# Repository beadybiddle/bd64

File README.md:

# bd64
64 key custom mechanical keyboard project. Successor to the BD83.

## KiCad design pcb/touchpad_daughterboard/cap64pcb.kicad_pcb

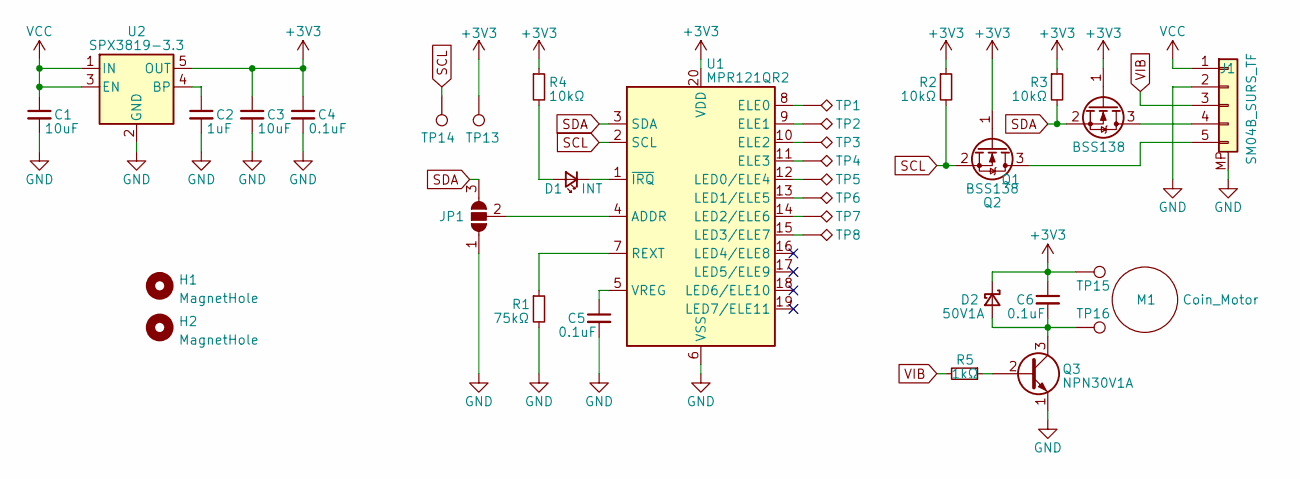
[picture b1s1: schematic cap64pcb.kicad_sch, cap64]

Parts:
C1, C3: 10uF; C_0805_2012Metric
C2: 1uF; C_0805_2012Metric
C4, C5, C6: 0.1uF; C_0805_2012Metric
D1: INT; LED_0603_1608Metric
D2: 50V1A; D_0805_2012Metric
H1, H2: MagnetHole; MountingHole_4mm
J1: SM04B_SURS_TF; JST_SUR_SM05B-SURS-TF_1x05-1MP_P0.80mm_Horizontal
JP1: SolderJumper_3_Open; SolderJumper-3_P1.3mm_Open_RoundedPad1.0x1.5mm_NumberLabels
M1: Coin_Motor; VC1018B001L
Q1, Q2: BSS138; SOT-23
Q3: NPN30V1A; SOT-23
R1: 75kΩ; R_0805_2012Metric
R2, R3, R4: 10kΩ; R_0805_2012Metric
R5: 1kΩ; R_0805_2012Metric
TP1: TestPoint_Alt; CAPPAD_11.4x11.6_1
TP2, TP3, TP4, TP5, TP6, TP7: TestPoint_Alt; CAPPAD_11.4x11.6_2
TP8: TestPoint_Alt; CAPPAD_11.4x11.6_3
TP13: b; TestPoint_Pad_D1.0mm
TP14: d; TestPoint_Pad_D1.0mm
TP15: +; TestPoint_Pad_1.0x1.0mm
TP16: -; TestPoint_Pad_1.0x1.0mm
U1: MPR121QR2; UQFN-20_3x3mm_P0.4mm
U2: SPX3819-3.3; SOT-23-5

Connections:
+3V3: C3.1, C4.1, C6.1, D2.1 (K), Q1.1 (G), Q2.1 (G), R2.1, R3.1, R4.1, TP13.1, TP15.1, U1.20 (VDD), U2.5 (OUT)
GND: C1.2, C2.2, C3.2, C4.2, C5.2, J1.2, J1.MP, JP1.1 (A), Q3.1 (E), R1.2, U1.6 (VSS), U2.2 (GND)
unnamed: C2.1, U2.4 (BP)
unnamed: C5.1, U1.5 (VREG)
unnamed: C6.2, D2.2 (A), Q3.3 (C), TP16.1
unnamed: D1.1 (K), U1.1 (~IRQ)
unnamed: D1.2 (A), R4.2
unnamed: J1.4, Q1.3 (D)
unnamed: J1.5, Q2.3 (D)
unnamed: JP1.2 (C), U1.4 (ADDR)
unnamed: Q3.2 (B), R5.1
unnamed: R1.1, U1.7 (REXT)
unnamed: TP1.1, U1.8 (ELE0)
unnamed: TP2.1, U1.9 (ELE1)
unnamed: TP3.1, U1.10 (ELE2)
unnamed: TP4.1, U1.11 (ELE3)
unnamed: TP5.1, U1.12 (LED0/ELE4)
unnamed: TP6.1, U1.13 (LED1/ELE5)
unnamed: TP7.1, U1.14 (LED2/ELE6)
unnamed: TP8.1, U1.15 (LED3/ELE7)
SCL: Q2.2 (S), R2.2, TP14.1, U1.2 (SCL)
SDA: JP1.3 (B), Q1.2 (S), R3.2, U1.3 (SDA)
VCC: C1.1, J1.1, U2.1 (IN), U2.3 (EN)
VIB: J1.3, R5.2

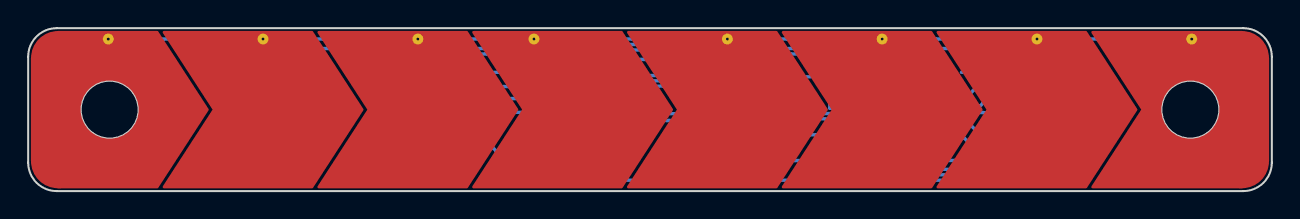
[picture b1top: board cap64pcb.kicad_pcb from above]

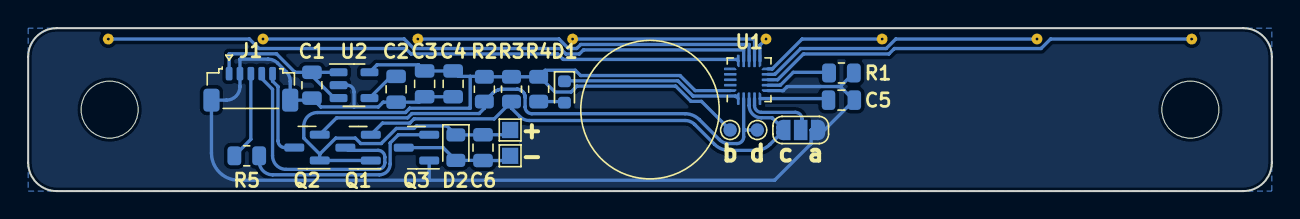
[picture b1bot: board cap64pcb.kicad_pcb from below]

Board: 2 copper layers, 91.6 x 12.0 mm, 35 parts (25 on the bottom side), 24 nets.

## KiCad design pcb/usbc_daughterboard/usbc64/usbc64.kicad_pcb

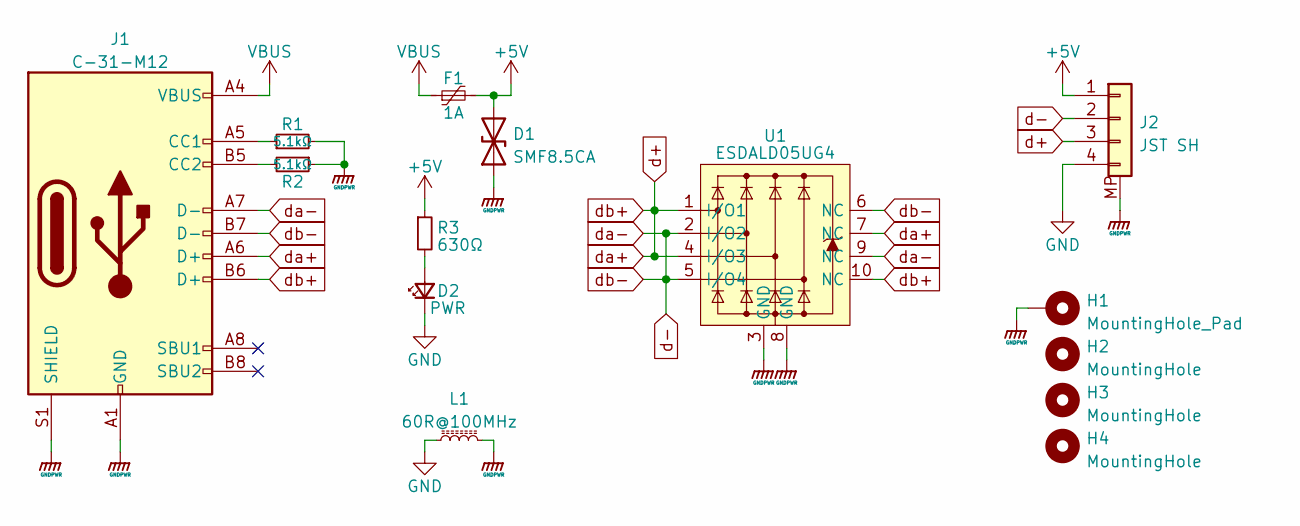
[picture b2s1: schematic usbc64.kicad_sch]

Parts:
D1: SMF8.5CA; D_SOD-123F
D2: PWR; LED_0603_1608Metric
F1: 1A; Fuse_1206_3216Metric
H1: MountingHole_Pad; MountingHole_2.2mm_M2_Pad
H2, H3, H4: MountingHole; MountingHole_2.2mm_M2_Pad
J1: C-31-M12; USB_C_Receptacle_HRO_TYPE-C-31-M-12
J2: JST SH; JST_SH_SM04B-SRSS-TB_1x04-1MP_P1.00mm_Horizontal
L1: 60R@100MHz; L_1206_3216Metric
R1, R2: 5.1kΩ; R_0603_1608Metric
R3: 630Ω; R_0603_1608Metric
U1: ESDALD05UG4

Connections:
+5V: D1.2 (A2), F1.2, J2.1, R3.1
GND: D2.1 (K), J2.4, L1.1
GNDPWR: D1.1 (A1), H1.1, J1.A1 (GND), J1.A12 (GND), J1.B1 (GND), J1.B12 (GND), J1.S1 (SHIELD), J2.MP, L1.2, R1.2, R2.1, U1.3 (GND), U1.8 (GND)
unnamed: D2.2 (A), R3.2
unnamed: J1.A5 (CC1), R1.1
unnamed: J1.B5 (CC2), R2.2
VBUS: F1.1, J1.A4 (VBUS), J1.A9 (VBUS), J1.B4 (VBUS), J1.B9 (VBUS)
d+: J1.A6 (D+), J1.B6 (D+), J2.3, U1.1 (I/O1), U1.4 (I/O3), U1.7 (NC), U1.10 (NC)
d-: J1.A7 (D-), J1.B7 (D-), J2.2, U1.2 (I/O2), U1.5 (I/O4), U1.6 (NC), U1.9 (NC)

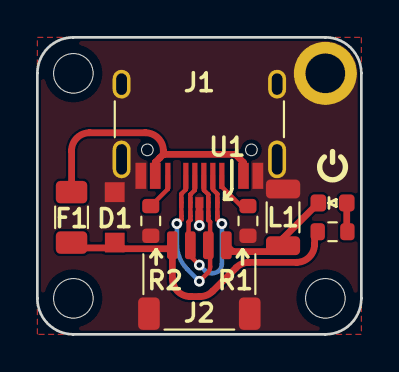
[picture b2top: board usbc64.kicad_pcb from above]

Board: 2 copper layers, 18.0 x 16.5 mm, 15 parts (1 on the bottom side), 9 nets.

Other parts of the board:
Ge: LOGO; usbc_back_silkraster

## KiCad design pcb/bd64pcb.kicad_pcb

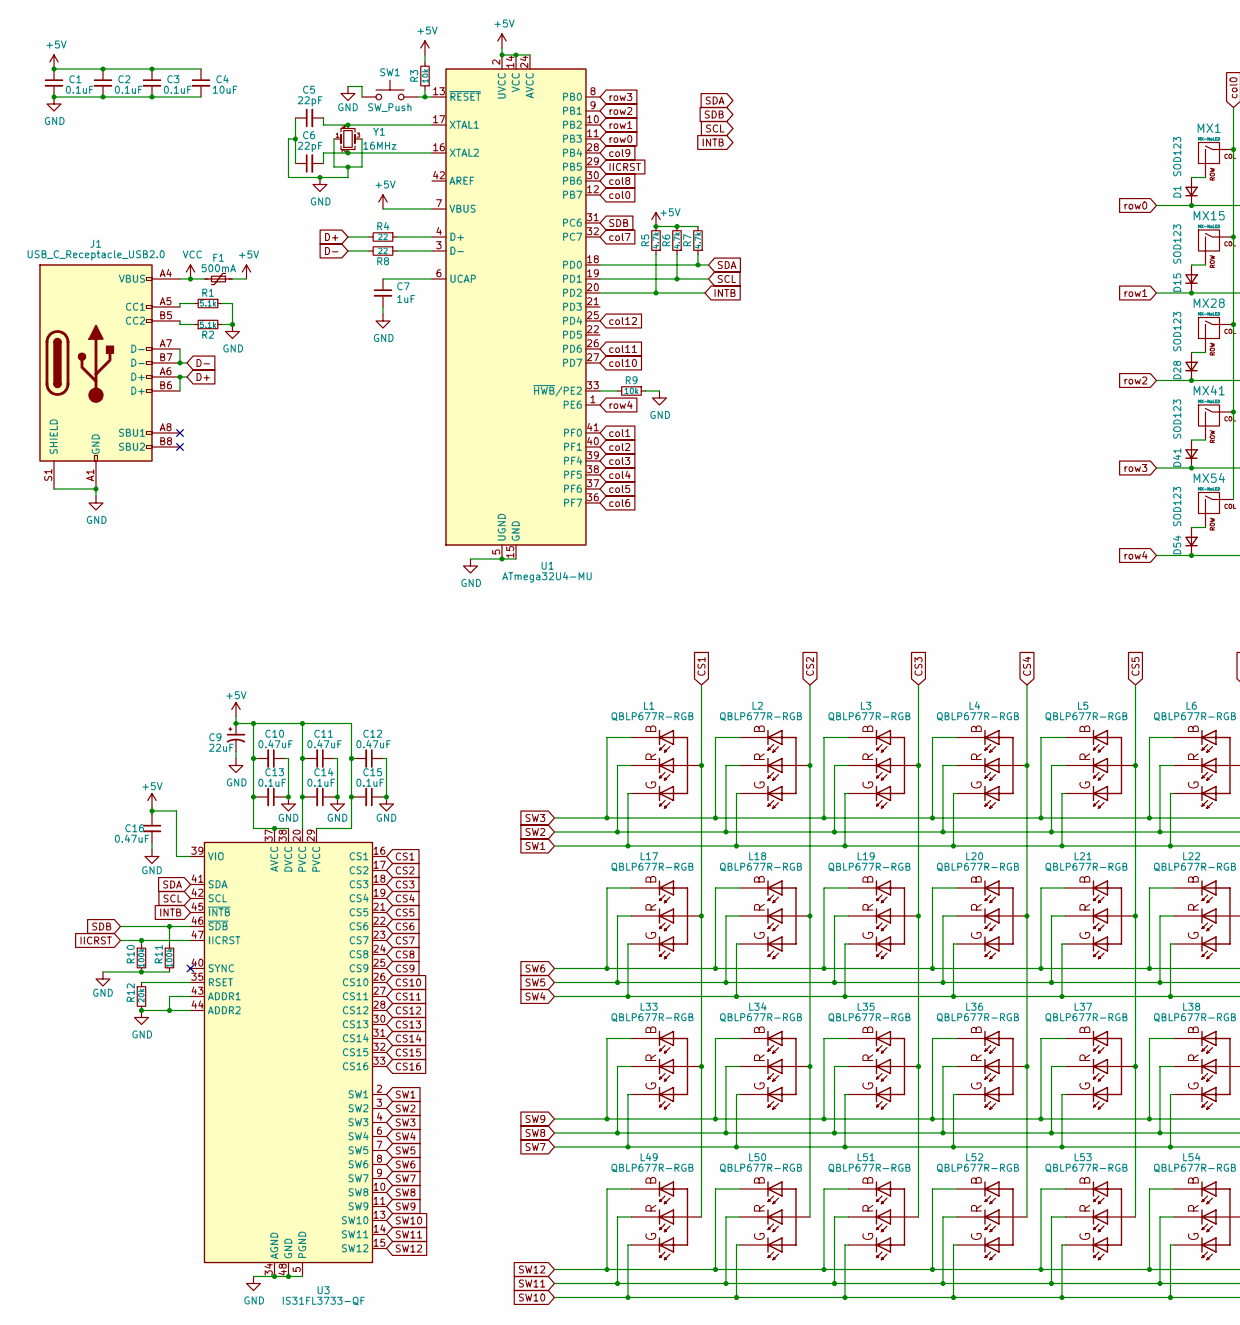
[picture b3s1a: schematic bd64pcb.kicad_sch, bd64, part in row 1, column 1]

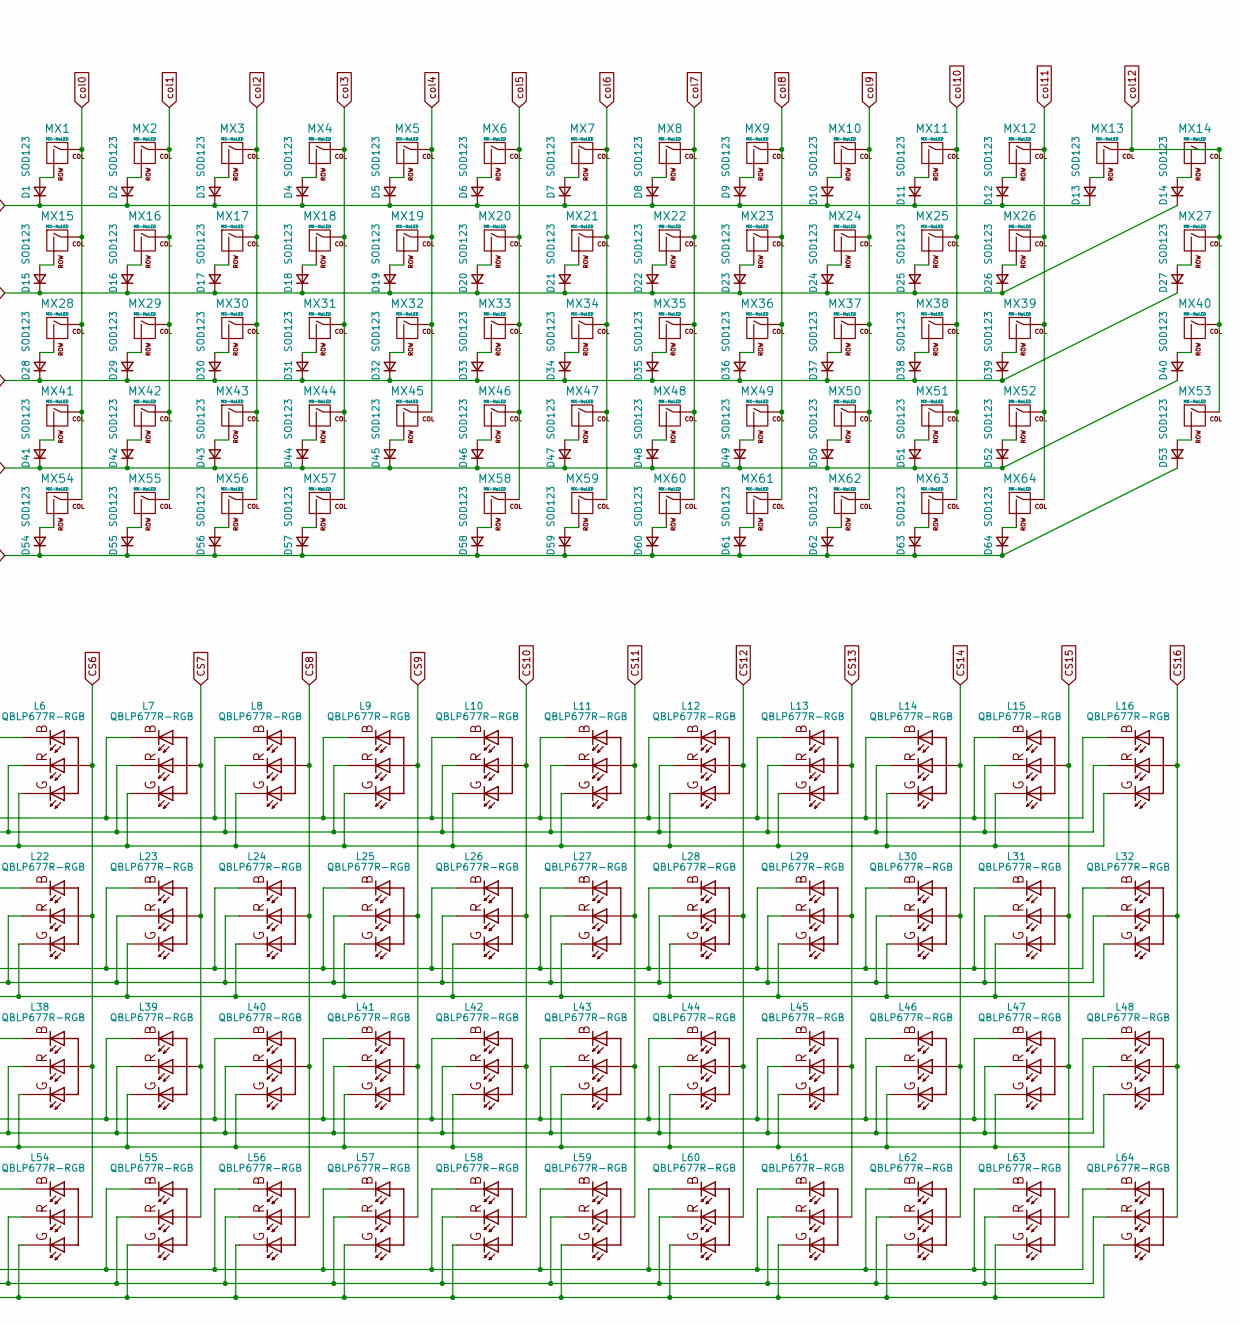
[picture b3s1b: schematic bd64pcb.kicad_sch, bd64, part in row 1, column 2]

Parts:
C1, C2, C3, C13, C14, C15: 0.1uF; C_0805_2012Metric
C4: 10uF; C_0805_2012Metric
C5, C6: 22pF; C_0805_2012Metric
C7: 1uF; C_0805_2012Metric
C9: 22uF; C_0805_2012Metric
C10, C11, C12, C16: 0.47uF; C_0805_2012Metric
D1, D2, D3, D4, D5, D6, D7, D8, D9, D10, D11, D12, D13, D14, D15, D16, D17, D18, D19, D20, D21, D22, D23, D24, D25, D26, D27, D28, D29, D30, D31, D32, D33, D34, D35, D36, D37, D38, D39, D40, D41, D42, D43, D44, D45, D46, D47, D48, D49, D50, D51, D52, D53, D54, D55, D56, D57, D58, D59, D60, D61, D62, D63, D64: SOD123; D_SOD-123
F1: 500mA; Fuse_1206_3216Metric
J1: USB_C_Receptacle_USB2.0; USB_C_Receptacle_GCT_USB4085
L1, L2, L3, L4, L5, L6, L7, L8, L9, L10, L11, L12, L13, L14, L15, L16, L17, L18, L19, L20, L21, L22, L23, L24, L25, L26, L27, L28, L29, L30, L31, L32, L33, L34, L35, L36, L37, L38, L39, L40, L41, L42, L43, L44, L45, L46, L47, L48, L49, L50, L51, L52, L53, L54, L55, L56, L57, L58, L59, L60, L61, L62, L63, L64: QBLP677R-RGB; RGB-REVERSE_MOUNT
MX1, MX2, MX3: MX-NoLED; MXOnly-1U-NoLED
MX4, MX5, MX6, MX7, MX8, MX9, MX10, MX11, MX12, MX13, MX14, MX16, MX17, MX18, MX19, MX20, MX21, MX22, MX23, MX24, MX25, MX26, MX29, MX30, MX31, MX32, MX33, MX34, MX35, MX36, MX37, MX38, MX39, MX42, MX43, MX44, MX45, MX46, MX47, MX48, MX49, MX50, MX51, MX52, MX58, MX59: MX-NoLED; MX-1U-NoLED
MX15, MX53, MX54, MX55, MX61, MX62, MX63, MX64: MX-NoLED; MX-1.25U-NoLED
MX27, MX41: MX-NoLED; MX-1.75U-NoLED
MX28, MX40, MX56, MX57, MX60: MX-NoLED; MX-1.5U-NoLED
R1, R2: 5.1k; R_0805_2012Metric
R3, R9: 10k; R_0805_2012Metric
R4, R8: 22; R_0805_2012Metric
R5, R6, R7: 4.7k; R_0805_2012Metric
R10, R11: 100k; R_0805_2012Metric
R12: 20k; R_0805_2012Metric
SW1: SW_Push; SKQG-1155865
U1: ATmega32U4-MU; QFN-44-1EP_7x7mm_P0.5mm_EP5.2x5.2mm
U3: IS31FL3733-QF; QFN-48-1EP_6x6mm_P0.4mm_EP4.2x4.2mm
Y1: 16MHz; Crystal_SMD_3225-4Pin_3.2x2.5mm

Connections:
+5V: C1.1, C2.1, C3.1, C4.1, C9.1, C10.2, C11.2, C12.2, C13.2, C14.2, C15.2, C16.1, F1.1, R3.2, R5.2, R6.2, R7.2, U1.2 (UVCC), U1.7 (VBUS), U1.14 (VCC), U1.24 (AVCC), U1.34 (VCC), U1.44 (AVCC), U3.20 (PVCC), U3.29 (PVCC), U3.37 (AVCC), U3.38 (DVCC), U3.39 (VIO)
CS1: L1.COMMON_ANODE, L17.COMMON_ANODE, L33.COMMON_ANODE, L49.COMMON_ANODE, U3.16 (CS1)
CS2: L2.COMMON_ANODE, L18.COMMON_ANODE, L34.COMMON_ANODE, L50.COMMON_ANODE, U3.17 (CS2)
CS3: L3.COMMON_ANODE, L19.COMMON_ANODE, L35.COMMON_ANODE, L51.COMMON_ANODE, U3.18 (CS3)
CS4: L4.COMMON_ANODE, L20.COMMON_ANODE, L36.COMMON_ANODE, L52.COMMON_ANODE, U3.19 (CS4)
CS5: L5.COMMON_ANODE, L21.COMMON_ANODE, L37.COMMON_ANODE, L53.COMMON_ANODE, U3.21 (CS5)
CS6: L6.COMMON_ANODE, L22.COMMON_ANODE, L38.COMMON_ANODE, L54.COMMON_ANODE, U3.22 (CS6)
CS7: L7.COMMON_ANODE, L23.COMMON_ANODE, L39.COMMON_ANODE, L55.COMMON_ANODE, U3.23 (CS7)
CS8: L8.COMMON_ANODE, L24.COMMON_ANODE, L40.COMMON_ANODE, L56.COMMON_ANODE, U3.24 (CS8)
CS9: L9.COMMON_ANODE, L25.COMMON_ANODE, L41.COMMON_ANODE, L57.COMMON_ANODE, U3.25 (CS9)
CS10: L10.COMMON_ANODE, L26.COMMON_ANODE, L42.COMMON_ANODE, L58.COMMON_ANODE, U3.26 (CS10)
CS11: L11.COMMON_ANODE, L27.COMMON_ANODE, L43.COMMON_ANODE, L59.COMMON_ANODE, U3.27 (CS11)
CS12: L12.COMMON_ANODE, L28.COMMON_ANODE, L44.COMMON_ANODE, L60.COMMON_ANODE, U3.28 (CS12)
CS13: L13.COMMON_ANODE, L29.COMMON_ANODE, L45.COMMON_ANODE, L61.COMMON_ANODE, U3.30 (CS13)
CS14: L14.COMMON_ANODE, L30.COMMON_ANODE, L46.COMMON_ANODE, L62.COMMON_ANODE, U3.31 (CS14)
CS15: L15.COMMON_ANODE, L31.COMMON_ANODE, L47.COMMON_ANODE, L63.COMMON_ANODE, U3.32 (CS15)
CS16: L16.COMMON_ANODE, L32.COMMON_ANODE, L48.COMMON_ANODE, L64.COMMON_ANODE, U3.33 (CS16)
D+: J1.A6 (D+), J1.B6 (D+), R4.2
D-: J1.A7 (D-), J1.B7 (D-), R8.2
GND: C1.2, C2.2, C3.2, C4.2, C5.1, C6.1, C7.2, C9.2, C10.1, C11.1, C12.1, C13.1, C14.1, C15.1, C16.2, J1.A1 (GND), J1.A12 (GND), J1.B1 (GND), J1.B12 (GND), J1.S1 (SHIELD), R1.1, R2.2, R9.1, R10.2, R11.2, R12.2, SW1.1, U1.5 (UGND), U1.15 (GND), U1.23 (GND), U1.35 (GND), U1.43 (GND), U1.45 (GND), U3.5 (PGND), U3.12 (PGND), U3.34 (AGND), U3.43 (ADDR1), U3.44 (ADDR2), U3.48 (GND), U3.49 (GND), Y1.1, Y1.3
IICRST: R10.1, U1.29 (PB5), U3.47 (IICRST)
INTB: R5.1, U1.20 (PD2), U3.45 (~INTB)
unnamed: C5.2, U1.17 (XTAL1), Y1.4
unnamed: C6.2, U1.16 (XTAL2), Y1.2
unnamed: C7.1, U1.6 (UCAP)
unnamed: D1.2 (A), MX1.2 (ROW)
unnamed: D2.2 (A), MX2.2 (ROW)
unnamed: D3.2 (A), MX3.2 (ROW)
unnamed: D4.2 (A), MX4.2 (ROW)
unnamed: D5.2 (A), MX5.2 (ROW)
unnamed: D6.2 (A), MX6.2 (ROW)
unnamed: D7.2 (A), MX7.2 (ROW)
unnamed: D8.2 (A), MX8.2 (ROW)
unnamed: D9.2 (A), MX9.2 (ROW)
unnamed: D10.2 (A), MX10.2 (ROW)
unnamed: D11.2 (A), MX11.2 (ROW)
unnamed: D12.2 (A), MX12.2 (ROW)
unnamed: D13.2 (A), MX13.2 (ROW)
unnamed: D14.2 (A), MX14.2 (ROW)
unnamed: D15.2 (A), MX15.2 (ROW)
unnamed: D16.2 (A), MX16.2 (ROW)
unnamed: D17.2 (A), MX17.2 (ROW)
unnamed: D18.2 (A), MX18.2 (ROW)
unnamed: D19.2 (A), MX19.2 (ROW)
unnamed: D20.2 (A), MX20.2 (ROW)
unnamed: D21.2 (A), MX21.2 (ROW)
unnamed: D22.2 (A), MX22.2 (ROW)
unnamed: D23.2 (A), MX23.2 (ROW)
unnamed: D24.2 (A), MX24.2 (ROW)
unnamed: D25.2 (A), MX25.2 (ROW)
unnamed: D26.2 (A), MX26.2 (ROW)
unnamed: D27.2 (A), MX27.2 (ROW)
unnamed: D28.2 (A), MX28.2 (ROW)
unnamed: D29.2 (A), MX29.2 (ROW)
unnamed: D30.2 (A), MX30.2 (ROW)
unnamed: D31.2 (A), MX31.2 (ROW)
unnamed: D32.2 (A), MX32.2 (ROW)
unnamed: D33.2 (A), MX33.2 (ROW)
unnamed: D34.2 (A), MX34.2 (ROW)
unnamed: D35.2 (A), MX35.2 (ROW)
unnamed: D36.2 (A), MX36.2 (ROW)
unnamed: D37.2 (A), MX37.2 (ROW)
unnamed: D38.2 (A), MX38.2 (ROW)
unnamed: D39.2 (A), MX39.2 (ROW)
unnamed: D40.2 (A), MX40.2 (ROW)
unnamed: D41.2 (A), MX41.2 (ROW)
unnamed: D42.2 (A), MX42.2 (ROW)
unnamed: D43.2 (A), MX43.2 (ROW)
unnamed: D44.2 (A), MX44.2 (ROW)
unnamed: D45.2 (A), MX45.2 (ROW)
unnamed: D46.2 (A), MX46.2 (ROW)
unnamed: D47.2 (A), MX47.2 (ROW)
unnamed: D48.2 (A), MX48.2 (ROW)
unnamed: D49.2 (A), MX49.2 (ROW)
unnamed: D50.2 (A), MX50.2 (ROW)
unnamed: D51.2 (A), MX51.2 (ROW)
unnamed: D52.2 (A), MX52.2 (ROW)
unnamed: D53.2 (A), MX53.2 (ROW)
unnamed: D54.2 (A), MX54.2 (ROW)
unnamed: D55.2 (A), MX55.2 (ROW)
unnamed: D56.2 (A), MX56.2 (ROW)
unnamed: D57.2 (A), MX57.2 (ROW)
unnamed: D58.2 (A), MX58.2 (ROW)
unnamed: D59.2 (A), MX59.2 (ROW)
unnamed: D60.2 (A), MX60.2 (ROW)
unnamed: D61.2 (A), MX61.2 (ROW)
unnamed: D62.2 (A), MX62.2 (ROW)
unnamed: D63.2 (A), MX63.2 (ROW)
unnamed: D64.2 (A), MX64.2 (ROW)
unnamed: J1.A5 (CC1), R1.2
unnamed: J1.B5 (CC2), R2.1
unnamed: R3.1, SW1.2, U1.13 (~RESET)
unnamed: R4.1, U1.4 (D+)
unnamed: R8.1, U1.3 (D-)
unnamed: R9.2, U1.33 (~HWB/PE2)
unnamed: R12.1, U3.35 (RSET)
SCL: R6.1, U1.19 (PD1), U3.42 (SCL)
SDA: R7.1, U1.18 (PD0), U3.41 (SDA)
SDB: R11.1, U1.31 (PC6), U3.46 (~SDB)
SW1: L1.2, L2.2, L3.2, L4.2, L5.2, L6.2, L7.2, L8.2, L9.2, L10.2, L11.2, L12.2, L13.2, L14.2, L15.2, L16.2, U3.2 (SW1)
SW2: L1.3, L2.3, L3.3, L4.3, L5.3, L6.3, L7.3, L8.3, L9.3, L10.3, L11.3, L12.3, L13.3, L14.3, L15.3, L16.3, U3.3 (SW2)
SW3: L1.1, L2.1, L3.1, L4.1, L5.1, L6.1, L7.1, L8.1, L9.1, L10.1, L11.1, L12.1, L13.1, L14.1, L15.1, L16.1, U3.4 (SW3)
SW4: L17.2, L18.2, L19.2, L20.2, L21.2, L22.2, L23.2, L24.2, L25.2, L26.2, L27.2, L28.2, L29.2, L30.2, L31.2, L32.2, U3.6 (SW4)
SW5: L17.3, L18.3, L19.3, L20.3, L21.3, L22.3, L23.3, L24.3, L25.3, L26.3, L27.3, L28.3, L29.3, L30.3, L31.3, L32.3, U3.7 (SW5)
SW6: L17.1, L18.1, L19.1, L20.1, L21.1, L22.1, L23.1, L24.1, L25.1, L26.1, L27.1, L28.1, L29.1, L30.1, L31.1, L32.1, U3.8 (SW6)
SW7: L33.2, L34.2, L35.2, L36.2, L37.2, L38.2, L39.2, L40.2, L41.2, L42.2, L43.2, L44.2, L45.2, L46.2, L47.2, L48.2, U3.9 (SW7)
SW8: L33.3, L34.3, L35.3, L36.3, L37.3, L38.3, L39.3, L40.3, L41.3, L42.3, L43.3, L44.3, L45.3, L46.3, L47.3, L48.3, U3.10 (SW8)
SW9: L33.1, L34.1, L35.1, L36.1, L37.1, L38.1, L39.1, L40.1, L41.1, L42.1, L43.1, L44.1, L45.1, L46.1, L47.1, L48.1, U3.11 (SW9)
SW10: L49.2, L50.2, L51.2, L52.2, L53.2, L54.2, L55.2, L56.2, L57.2, L58.2, L59.2, L60.2, L61.2, L62.2, L63.2, L64.2, U3.13 (SW10)
SW11: L49.3, L50.3, L51.3, L52.3, L53.3, L54.3, L55.3, L56.3, L57.3, L58.3, L59.3, L60.3, L61.3, L62.3, L63.3, L64.3, U3.14 (SW11)
SW12: L49.1, L50.1, L51.1, L52.1, L53.1, L54.1, L55.1, L56.1, L57.1, L58.1, L59.1, L60.1, L61.1, L62.1, L63.1, L64.1, U3.15 (SW12)
VCC: F1.2, J1.A4 (VBUS), J1.A9 (VBUS), J1.B4 (VBUS), J1.B9 (VBUS)
col0: MX1.1 (COL), MX15.1 (COL), MX28.1 (COL), MX41.1 (COL), MX54.1 (COL), U1.12 (PB7)
col1: MX2.1 (COL), MX16.1 (COL), MX29.1 (COL), MX42.1 (COL), MX55.1 (COL), U1.41 (PF0)
col2: MX3.1 (COL), MX17.1 (COL), MX30.1 (COL), MX43.1 (COL), MX56.1 (COL), U1.40 (PF1)
col3: MX4.1 (COL), MX18.1 (COL), MX31.1 (COL), MX44.1 (COL), MX57.1 (COL), U1.39 (PF4)
col4: MX5.1 (COL), MX19.1 (COL), MX32.1 (COL), MX45.1 (COL), U1.38 (PF5)
col5: MX6.1 (COL), MX20.1 (COL), MX33.1 (COL), MX46.1 (COL), MX58.1 (COL), U1.37 (PF6)
col6: MX7.1 (COL), MX21.1 (COL), MX34.1 (COL), MX47.1 (COL), MX59.1 (COL), U1.36 (PF7)
col7: MX8.1 (COL), MX22.1 (COL), MX35.1 (COL), MX48.1 (COL), MX60.1 (COL), U1.32 (PC7)
col8: MX9.1 (COL), MX23.1 (COL), MX36.1 (COL), MX49.1 (COL), MX61.1 (COL), U1.30 (PB6)
col9: MX10.1 (COL), MX24.1 (COL), MX37.1 (COL), MX50.1 (COL), MX62.1 (COL), U1.28 (PB4)
col10: MX11.1 (COL), MX25.1 (COL), MX38.1 (COL), MX51.1 (COL), MX63.1 (COL), U1.27 (PD7)
col11: MX12.1 (COL), MX26.1 (COL), MX39.1 (COL), MX52.1 (COL), MX64.1 (COL), U1.26 (PD6)
col12: MX13.1 (COL), MX14.1 (COL), MX27.1 (COL), MX40.1 (COL), MX53.1 (COL), U1.25 (PD4)
row0: D1.1 (K), D2.1 (K), D3.1 (K), D4.1 (K), D5.1 (K), D6.1 (K), D7.1 (K), D8.1 (K), D9.1 (K), D10.1 (K), D11.1 (K), D12.1 (K), D13.1 (K), U1.11 (PB3)
row1: D14.1 (K), D15.1 (K), D16.1 (K), D17.1 (K), D18.1 (K), D19.1 (K), D20.1 (K), D21.1 (K), D22.1 (K), D23.1 (K), D24.1 (K), D25.1 (K), D26.1 (K), U1.10 (PB2)
row2: D27.1 (K), D28.1 (K), D29.1 (K), D30.1 (K), D31.1 (K), D32.1 (K), D33.1 (K), D34.1 (K), D35.1 (K), D36.1 (K), D37.1 (K), D38.1 (K), D39.1 (K), U1.9 (PB1)
row3: D40.1 (K), D41.1 (K), D42.1 (K), D43.1 (K), D44.1 (K), D45.1 (K), D46.1 (K), D47.1 (K), D48.1 (K), D49.1 (K), D50.1 (K), D51.1 (K), D52.1 (K), U1.8 (PB0)
row4: D53.1 (K), D54.1 (K), D55.1 (K), D56.1 (K), D57.1 (K), D58.1 (K), D59.1 (K), D60.1 (K), D61.1 (K), D62.1 (K), D63.1 (K), D64.1 (K), U1.1 (PE6)

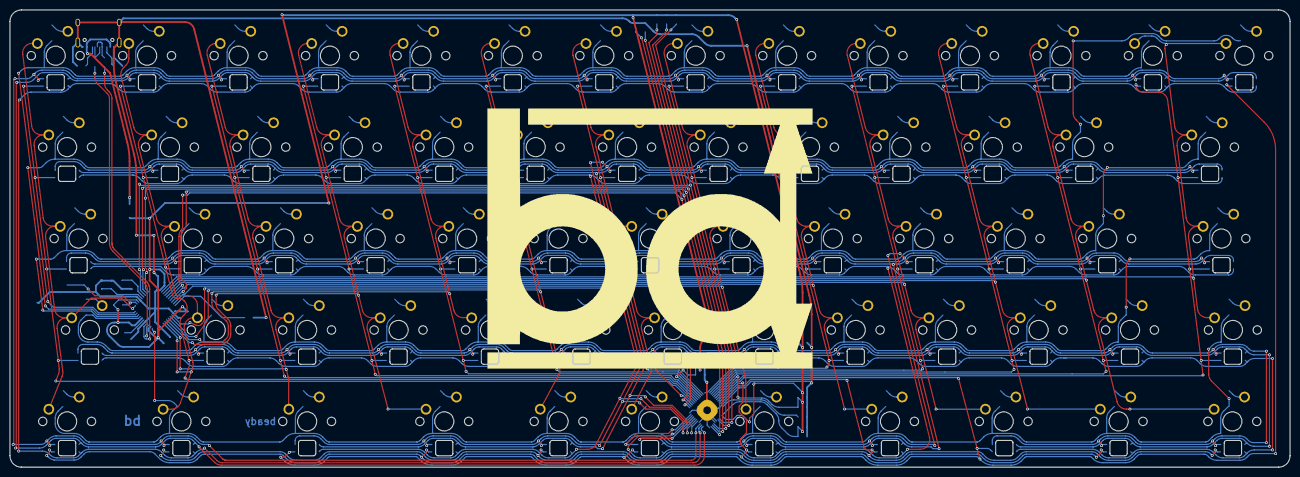
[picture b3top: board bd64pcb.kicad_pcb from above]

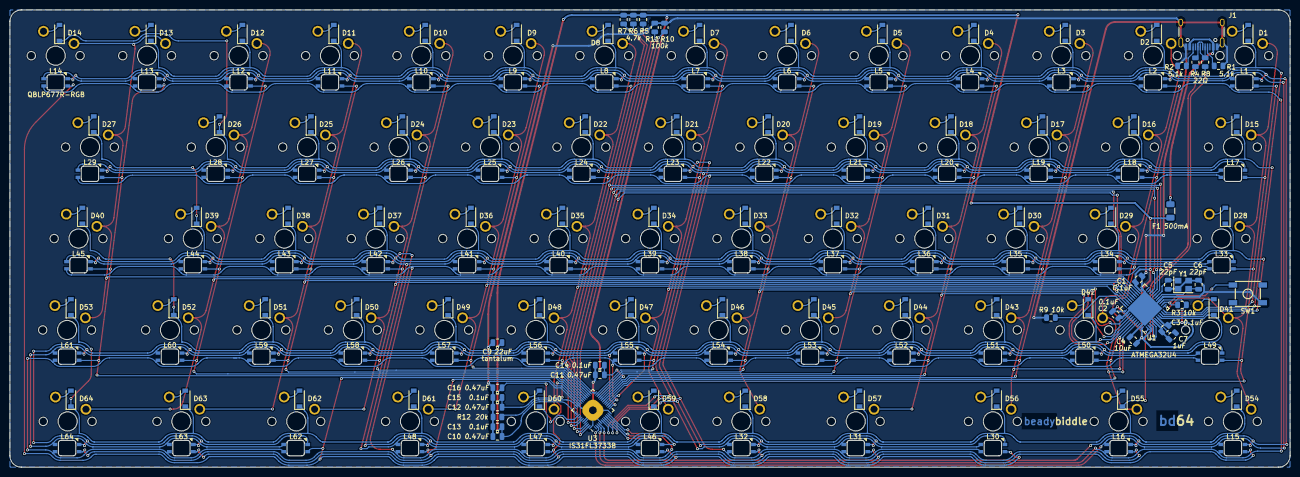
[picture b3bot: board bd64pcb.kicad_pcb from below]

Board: 2 copper layers, 266.7 x 95.2 mm, 225 parts (161 on the bottom side), 130 nets.

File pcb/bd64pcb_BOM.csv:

"Id";"Designator";"Package";"Quantity";"Designation";"Supplier and ref";
1;"MX1,MX2,MX4,MX10,MX11,MX12,MX13,MX14,MX16,MX17,MX18,MX19,MX20,MX25,MX26,MX29,MX37,MX38,MX39,MX42,MX43,MX44,MX45,MX46,MX47,MX48,MX49,MX50,MX51,MX52,MX58,MX59,MX30,MX36,MX35,MX34,MX33,MX32,MX31,MX23,MX22,MX21,MX5,MX9,MX24,MX7,MX6,MX8,MX3";"MXOnly-1U-NoLED";49;"MX-NoLED";;;
2;"MX15,MX54,MX55,MX61,MX62,MX63,MX64,MX53";"MXOnly-1.25U-NoLED";8;"MX-NoLED";;;
3;"MX28,MX40,MX56,MX57,MX60";"MXOnly-1.5U-NoLED";5;"MX-NoLED";;;
4;"MX41,MX27";"MXOnly-1.75U-NoLED";2;"MX-NoLED";;;
5;"C1,C2,C3,C13,C14,C15";"C_0805_2012Metric";6;"0.1uF";;;
6;"C4";"C_0805_2012Metric";1;"10uF";;;
7;"C5,C6";"C_0805_2012Metric";2;"22pF";;;
8;"C7,C8";"C_0805_2012Metric";2;"1uF";;;
9;"C9";"C_0805_2012Metric";1;"22uF";;;
10;"C10,C11,C12,C16";"C_0805_2012Metric";4;"0.47uF";;;
11;"D2,D3,D4,D5,D6,D7,D8,D9,D10,D11,D12,D13,D15,D16,D17,D18,D19,D20,D21,D22,D23,D24,D25,D26,D14,D28,D29,D30,D31,D32,D33,D34,D35,D36,D37,D38,D39,D27,D41,D42,D43,D44,D45,D46,D47,D48,D49,D50,D51,D52,D40,D54,D55,D56,D57,D58,D59,D60,D61,D62,D63,D64,D53,D1";"D_SOD-123";64;"SOD123";;;
12;"F1";"Fuse_1206_3216Metric";1;"500mA";;;
13;"L1,L2,L3,L4,L5,L6,L7,L8,L9,L10,L11,L12,L13,L14,L15,L16,L18,L19,L20,L21,L22,L23,L24,L25,L26,L27,L28,L29,L30,L31,L32,L33,L34,L35,L36,L37,L38,L39,L40,L41,L42,L43,L44,L45,L46,L47,L48,L49,L50,L51,L52,L53,L54,L55,L56,L57,L58,L59,L60,L61,L62,L63,L64,L17";"RGB-REVERSE_MOUNT";64;"QBLP677R-RGB";;;
14;"R1,R2";"R_0805_2012Metric";2;"5.1k";;;
15;"R3,R9";"R_0805_2012Metric";2;"10k";;;
16;"R5,R7,R6";"R_0805_2012Metric";3;"4.7k";;;
17;"R8,R4";"R_0805_2012Metric";2;"22";;;
18;"R10,R11";"R_0805_2012Metric";2;"100k";;;
19;"R12";"R_0805_2012Metric";1;"20k";;;
20;"SW1";"SKQG-1155865";1;"SW_Push";;;
21;"TP1,TP4,TP7,TP17,TP10,TP18,TP5,TP2,TP8,TP15,TP16,TP9,TP12,TP6,TP13,TP14,TP3,TP11";"TestPoint_Plated_Hole_D2.0mm";18;"TestPoint";;;
22;"U3";"QFN-48-1EP_6x6mm_P0.4mm_EP4.2x4.2mm";1;"IS31FL3733-QF";;;
23;"Y1";"Crystal_SMD_3225-4Pin_3.2x2.5mm";1;"16MHz";;;
24;"U1";"QFN-44-1EP_7x7mm_P0.5mm_EP5.2x5.2mm";1;"ATmega32U4-MU";;;
25;"U2";"QFN-28-1EP_6x6mm_P0.65mm_EP4.25x4.25mm";1;"MCP23017_ML";;;
26;"J1";"USB_C_Receptacle_Palconn_UTC16-G";1;"USB_C_Receptacle_USB2.0";;;

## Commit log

2022-05-30 create pcb proj
2022-05-30 ai03 submodules (switch & misc)
2022-05-30 res w/ RGB footprint
2022-05-30 remove html QBL doc
2022-05-30 removing submodules
2022-05-30 re-adding submodules
2022-05-30 symbol & footprint libs
2022-05-30 mcu schematic
2022-05-31 switch matrix & usbc prep
2022-06-01 mcp expander
2022-06-01 numbering components
2022-06-01 assigning footprints
2022-06-01 switches placed
2022-06-01 finna autoroute
2022-06-01 diodes placed
2022-06-01 flipped diodes and LEDs to rear
2022-06-02 LEDS place (poorly) and MCP footprint changed to QFN
2022-06-02 shifted diodes & LEDs, added preliminary edge cuts
2022-06-02 diodes mostly routed, rearranging LEDs
2022-06-02 no good traces yet
2022-06-02 boring switch traces
2022-06-02 first non45 trace down
2022-06-02 boring traces on most LEDs. updated to kicad 6
2022-06-02 still tracing LEDs
2022-06-02 shifted diodes over a tad
2022-06-02 removed all traces. restarting
2022-06-03 curves in progress
2022-06-03 easy LEDs routed
2022-06-03 easy diodes routed
2022-06-03 routed some right side LEDs
2022-06-03 more LED routing
2022-06-03 almost done with bottom row
2022-06-04 routing bottom LEDs
2022-06-04 rotated diode silks
2022-06-04 figuring out bottom LED SW pins
2022-06-04 matrices routed
2022-06-05 LED cols routed. ISSI caps and LED rows in progress
2022-06-05 cleaning up left and right edges
2022-06-05 fixing hole clearance errors
2022-06-05 removed solder jumpers. addresses are now fixed.
2022-06-05 issi tant cap in place. SW traces pending.
2022-06-07 idek
2022-06-09 connecting ISSI ground sink
2022-06-10 gitignore
2022-06-10 IIC lines from ISSI
2022-06-10 routing switch cols
2022-06-11 finna delete mcp
2022-06-11 mcp delet
2022-06-11 sw1-3 routed
2022-06-11 fixing gitignore file extension
2022-06-11 propagating gitignore change
2022-06-12 led SW pins routed
2022-06-12 cleaning up loose ends
2022-06-12 switch rows routed
2022-06-12 interconnected MCU grounds
2022-06-12 more descriptive cap silkscreen
2022-06-12 general cleanup (prep, silks)
2022-06-12 italicized values
2022-06-12 I2C pullups and pulldowns
2022-06-12 prettying i2c lines
2022-06-12 misc
2022-06-12 rows, cols, and i2c routed
2022-06-12 change and relocate usbc footprint
2022-06-12 clean usbc footprint and some fillets
2022-06-12 bd logo
2022-06-12 bd logo on pcb
2022-06-12 silk text to jlc spec
2022-06-12 vanity silk
2022-06-12 more informative silk
2022-06-13 everything connected and all errors/warnings resolved
2022-06-13 fillet touchups
2022-06-13 misc touchups
2022-06-13 back gnd fill
2022-06-13 unblocking vanity text from fill
2022-06-13 stitch vias
2022-06-13 remove big logo
2022-06-13 ignore photoshop files
2022-06-13 small logo
2022-06-13 purge extra logo bmp
2022-06-13 anti-loop stitches around dpair
2022-06-13 more silkscreen bs
2022-06-13 board dims silkscreen
2022-06-13 bigger silk text, removed component reference silks, added caution label
2022-06-13 plate and pcb models
2022-06-13 hidden diode reference silk
2022-06-13 hidden LED reference silks
2022-06-13 re-add LED ref silks
2022-06-13 decluttering silk labels with arrows
2022-06-13 more arrows, less clutter
2022-06-13 shrunk logo and rearranged for balance
2022-06-13 usbc receptacle 3d model
2022-06-13 diode 3d model
2022-06-13 sk6812mini-e 3d model (stand-in for QBL LEDs)
2022-06-13 cap 3d models
2022-06-13 chips and xtal 3d models
2022-06-13 mx switch 3d models
2022-06-13 all relevant mx footprints have 3d model
2022-06-13 silk touchup and pcb step export
2022-06-13 early concept render
2022-06-13 dirty ignore submodule changes
2022-06-14 reset switch silk label
2022-06-23 mounting posts first draft
2022-06-23 better post cutouts
2022-06-23 smaller traces rerouted around post cutouts
2022-06-23 all traces rerouted around cutouts. no errors/warnings.
2022-06-23 reorg
2022-06-23 old kicad version files purge
2022-06-23 rough JST placements
2022-06-23 update sch footprints, add 6.25 space opt
2022-06-23 fix space row misalignments, draft alt space row
2022-06-23 scrapping alt space layout
2022-06-23 more pullup value silks
2022-06-23 add Ω to sch values
2022-06-23 usbc removed; surrogate jst connected
2022-06-23 J3 connected and D+/- width fixed
2022-06-23 repaired stitching
2022-06-23 pcb subfolders
2022-06-23 migrate touchpad daughterboard files
2022-06-23 update touchpad footprint paths
2022-06-24 still stuck on jst orientation
2022-06-24 organizing sch components
2022-06-24 removing alt connectors
2022-06-24 5v thru 10uF as god intended
2022-06-24 connector silk labels and access cuts
2022-06-27 usbc begins
2022-06-28 6.25 space option added. stab collisions resolved.
2022-06-28 ISSI and LED shifted for 6.25 space footprint
2022-06-28 ISSI AVCC and DVCC connected
2022-06-28 remove IC ref des silks
2022-06-28 prettier space switch footprint
2022-06-28 soldermask color and JLC serial tag
2022-06-29 sch and pcb rough starts
2022-06-29 mounting holes
2022-06-29 gndpwr fills
2022-06-29 mounting hole clearances
2022-07-01 TVS picked
2022-07-01 esdald05ug4 footprint
2022-07-01 esdald05ug4 symbol
2022-07-01 esdald05ug4 footprint in lib
2022-07-01 NC pins to passive and tied a/b data lines
2022-07-01 rotate ferrite and connect vbus
2022-07-01 embiggen pads
2022-07-01 split gnd pads and tighten gaps
2022-07-01 split gnd pin
2022-07-01 sch misalignment
2022-07-01 data traces laid
2022-07-01 disconnect MP pads
2022-07-01 silk values instead of refdes
2022-07-01 placeholder fuse footprint and Imax
2022-07-02 add SH connector
2022-07-02 MP pads to GNDPWR
2022-07-02 having trouble sourcing connectors
2022-07-02 JST-SH & logo & traces routed
2022-07-02 jst sh 3d model
2022-07-02 diff layout + tvs diode
2022-07-03 ref des silks, status LED, LED resistor, 0603 footprints, all routed
2022-07-03 Ω symbol for resistor value
2022-07-03 cleaner diode silks
2022-07-03 ESDALD05UG4 3d model
2022-07-03 backside vanity logo
2022-07-03 usbc board step
2022-07-03 0603 LED footprint
2022-07-03 usbc prefs
2022-07-03 cap64 step export
2022-07-03 usbc connector from SUR to SH
2022-07-03 update connector values
2022-07-03 motherboard step export
2022-07-03 no pads on floating mounting holes
2022-07-03 connect MP pads to ground plane
2022-07-03 bidir zener diode value
2022-07-04 plategen (unused)
2022-07-04 simpler JST value silk
2022-07-06 prefs
2022-07-06 removing exposed copper from window area
2022-07-07 magnets with DRC errors lmao
2022-07-07 ignoring MH DRC
2022-07-07 touchpad STEP w/ MH
2022-07-07 MH values
2022-07-07 asdf
2022-07-08 rm random holes and reduce top post cutouts
2022-07-08 prepping edge cuts
2022-07-09 9.525mm corners
2022-07-09 no idea what changed lmao
2022-07-09 prep for alternate space rows
2022-07-09 5pin touchpad connector sch
2022-07-10 sm05b footprints and 3d models
2022-07-10 netclass chaos
2022-07-10 alt space row complete, RGB pending
2022-07-10 5pin jst sur
2022-07-10 reorder and reroute connector
2022-07-10 mcp moved
2022-07-11 space made for coin motor
2022-07-11 ERM symbol/footprint/3d model
2022-07-11 erm footprint update, all routed, no errors
2022-07-11 silks
2022-07-11 update touchpad step
2022-07-11 IRQ > VIB
2022-07-11 L46 to fit SW59
2022-07-11 L64 to fit SW64
2022-07-11 L63 to fit SW63
2022-07-11 L62 to fit SW62ab
2022-07-11 space row routed. no errors.
2022-07-11 more intuitive L48 silk
2022-07-11 3d models to pretty layout
2022-07-11 shift over gummy post
2022-07-11 front touchpad wire slot
2022-07-11 6.25 and jlcjlc silks
2022-07-11 mobo step update
2022-07-11 JLC order no. tag
2022-07-11 jlc order no tag
2022-07-12 ugly mobo w/ round cutouts
2022-07-12 ugly step
2022-07-12 removed board dim silks
2022-07-12 thinner usbc block
2022-07-13 even thinner usbc blok
2022-07-13 HWB to DPDT pushbutton
2022-07-13 remove touchpad drawings
2022-07-13 silkscreen raster for custom font
2022-07-13 remove jlcjlcjlcjlc
2022-07-13 usbc silk raster
2022-07-13 touchpad silk raster
2022-07-13 hiding values
2022-07-13 motor peripherals
2022-07-14 jfc what a mess
2022-07-14 mht symbols & footprint
2022-07-14 abhorrent rerouting. no errors/warnings
2022-07-15 remove mht 3d model
2022-07-15 mobo step w/o led models
2022-07-15 first gerber
2022-07-15 f_mask preview issue present
2022-08-03 11.4x11.6 pads
2022-08-03 hanging changes
2022-08-03 11.4 individuals
2022-08-04 removing 7.6x7.6 footprints
2022-08-04 pcb update
2022-08-04 nc pin and DRC check
